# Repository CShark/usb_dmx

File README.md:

# USB ArtNET Interface

This project is a USB ArtNET interface with four ports, based on the STM32G484. It will register itself as an Ethernet Card using the CDC-NCM protocoll to be automatically recognized by most operating systems (except Windows 10, which needs some manual configuration). It will then bind the ArtNET-implementation to a configurable IP on that virtual ethernet card. The device can be configured either using ArtNET commands for software that supports this, using a web interface on the device and it can optionally be extended to include a display module for configuration directly at the device.

## Schematic
The project uses an STM32G484RE, but should work with any STM32G4xxRE variant. The ports are controlled by a MAX3440E each, which will provide some ESD protection in addition to the TVS-Diodes. The device will draw around ~150mA, which is easily delivered by USB2.0 ports. Galvanic isolation was omitted because it needs too much space and because it is not recommended for the transmitting ports of DMX-Devices anyway (although it is recommended for receiving ports, but not mandatory).

## PCB
The PCB is designed as a four layer board, as with this small size the price was acceptable. The pcb was designed with a `TEKAL 31.29`-case from TEKO in mind, but any case with at least 100x100mm will work.  placing three ports at the rear and one port beside the usb port at the front of the case. The display module is completely optional and is designed to slot into the mainboard and is secured with an additional screw from the front. It is then connected using a 10-pin ribbon cable.

### BOM
The total cost for this device is currently aproximately 90€. Assembly takes around 6 hours, including soldering the boards, CNC the covers and soldering / crimping the connectors. You can save money by printing your own case (25€), finding a cheaper STM32G4xxRE variant at your local dealer (11€), finding cheaper XLR connectors (5€) and skipping on the display module (5€). 

<details>
<summary>Mainboard (~40€)</summary>

| Amount | Type | Value | Footprint |
|-|-|-|-|
| 4 | Capacitor | 1μF | 0603 |
| 7 | Capacitor | 100nF | 0603 |
| 2 | Capacitor | 20pF | 0603 |
| 1 | Capacitor | 10nF | 0603 |
| 1 | Capacitor | 4.7μF | 0603 |
| 8 | TVS Diode | | SMA |
| 1 | USB-C Receptacle | | |
| 1 | FFC Connector | | 1x10, Pitch 1mm |
| 4 | Terminal Block | | 1x3, Pitch 2.54mm |
| 1 | Pin Header | | 1x3, Pitch 2.54mm |
| 1 | Jumper | | 1x2, Pitch 2.54mm |
| 2 | Resistor | 5K1 | 0603 |
| 1 | Resistor | 4K7 | 0603 |
| 4 | Resistor | 130 | 0603 |
| 8 | Resistor | 560 | 0603 |
| 1 | Switch | | Through Hole, Height 6mm |
| 1 | Switch | | Through Hole, Angled, Height 6mm |
| 1 | DIP-Switch | | Through Hole, 2x4, Pitch 2.54mm |
| 1 | ESD Protection | ESDALD05UD4 | SOT23-6 |
| 1 | Linear Regulator | AP2112K-3.3 | SOT23-5 |
| 4 | Transceiver | MAX3440E | SOIC-8 |
| 1 | Crystal | 25MHz | HC49 |
| 1 | μC | STM32G484RE | LQFP64 |
    
</details>

<details>
<summary>Display Board (~5€)</summary>

| Amount | Type | Footprint |
|-|-|-|
| 1 | OLED-Display | 0.96" with I²C and SSD1306 compatible driver |
| 1 | FFC Connector | 1x10, Pitch 1mm |
| 2 | Resistor | 4K7 | 0603 |
| 4 | Switch | Through Hole, Height 10mm |
| 1 | FFC Cable | 1x10, Pitch 1mm, Length ~100mm, Type B (opposing-side contacts) |

</details>

<details>
<summary>Mechanical parts (~40€)</summary>

| Amount | Type | Specs |
|-|-|-|
| 1 | Case | TEKO TEKAL 31.29, or any case that takes Eurocard-sized PCBs (100x100mm) |
| 4 | XLR Connector | An individual mix of Female and Male XLR 3- and 5-Pin connectors, depending on your needs |
| 9 | Screws | M2, Length 15mm, Countersink |
| 9 | Nuts | M2 |
| 1 | Acrylic Window | 15mm x 25mm |
| 1 | Spacer | M2, Length 6mm |
| 1 | Mainboard PCB | | 
| 1 | Display PCB | |

</details>

Here are two lists on digikey that include all necessary components, except for the mechanical parts and the oled-display. It does contain four XLR-Connectors though.
- [Parts for the Mainboard](https://www.digikey.com/en/mylists/list/8UBRGNUC4X)
- [Parts for the Display-Module](https://www.digikey.com/en/mylists/list/5N5ETFD0BY)

## Firmware
The firmware is completely custom, only based on CMSIS (no HAL) and supports the important parts of the ArtNET protocol. Which port is an input and which an output can be set using the dip switches, but later be overwritten using either ArtNET commands, the WebUI or the display menu. The device also has a reset button to reset the configuration for when things go completely wrong. If the device is completely bricked it can be put into bootloader mode using a jumper on the mainboard.

The device supports mDNS and is always reachable using `artnet.local` in addition to its ip-address. The WebUI allows configuring each individual port with all the settings that ArtNET-Commands also support. You can also change the ip-configuration of the device and its internal minimal DHCP-Server, as well as clearing all settings, rebooting the device and switching the device into DFU/Bootloader mode to flash a new firmware.

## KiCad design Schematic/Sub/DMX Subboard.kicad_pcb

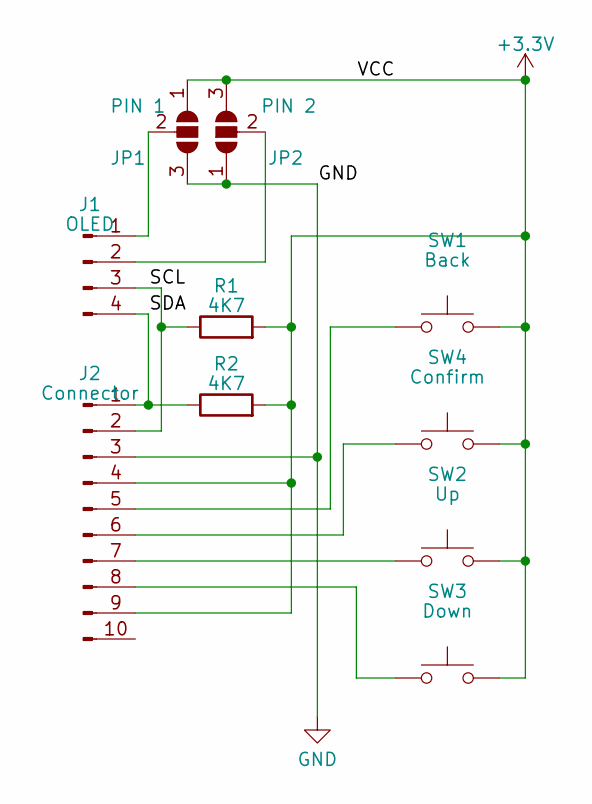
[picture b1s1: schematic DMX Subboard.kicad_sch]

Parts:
J1: OLED; PinHeader_1x04_P2.54mm_Vertical
J2: Connector; TE_1-84952-0_1x10-1MP_P1.0mm_Horizontal
JP1: PIN 1; SolderJumper-3_P2.0mm_Open_TrianglePad1.0x1.5mm
JP2: PIN 2; SolderJumper-3_P2.0mm_Open_TrianglePad1.0x1.5mm
R1, R2: 4K7; R_0603_1608Metric_Pad0.98x0.95mm_HandSolder
SW1: Back; SW_PUSH_6mm_H8.5mm
SW2: Up; SW_PUSH_6mm_H8.5mm
SW3: Down; SW_PUSH_6mm_H8.5mm
SW4: Confirm; SW_PUSH_6mm_H8.5mm

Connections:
+3.3V: J2.4, J2.9, JP1.1 (A), JP2.3 (B), R1.2, R2.2, SW1.2, SW2.2, SW3.2, SW4.2
/SCL: J1.3, J2.2, R1.1
/SDA: J1.4, J2.1, R2.1
GND: J2.3, JP1.3 (B), JP2.1 (A)
unnamed: J1.1, JP1.2 (C)
unnamed: J1.2, JP2.2 (C)
unnamed: J2.5, SW1.1
unnamed: J2.6, SW4.1
unnamed: J2.7, SW2.1
unnamed: J2.8, SW3.1

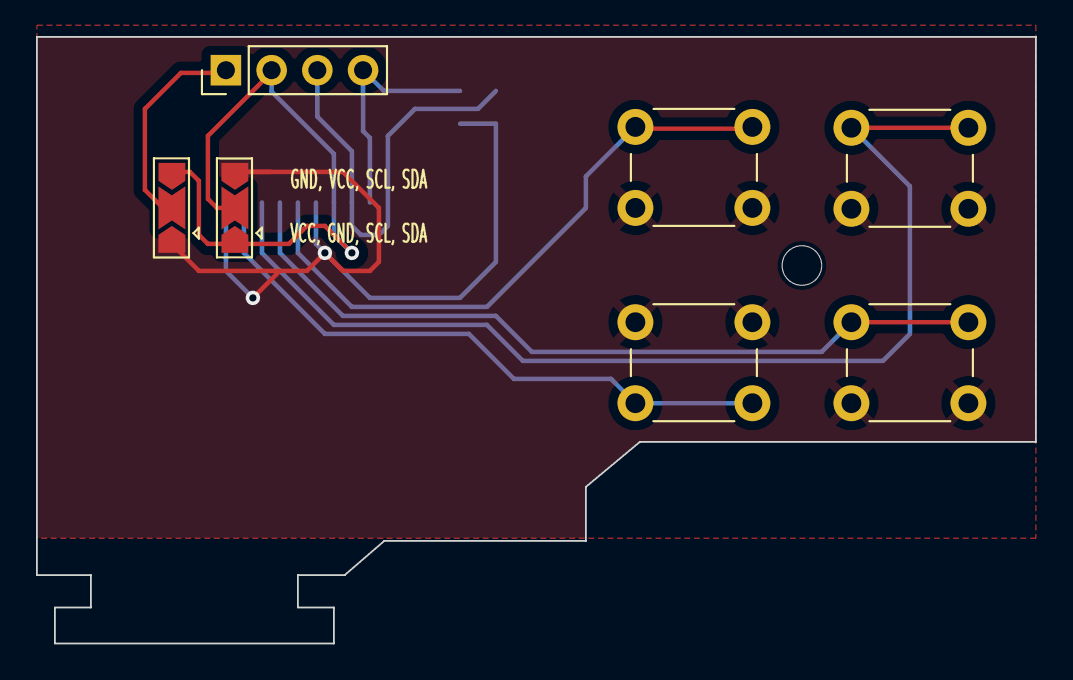
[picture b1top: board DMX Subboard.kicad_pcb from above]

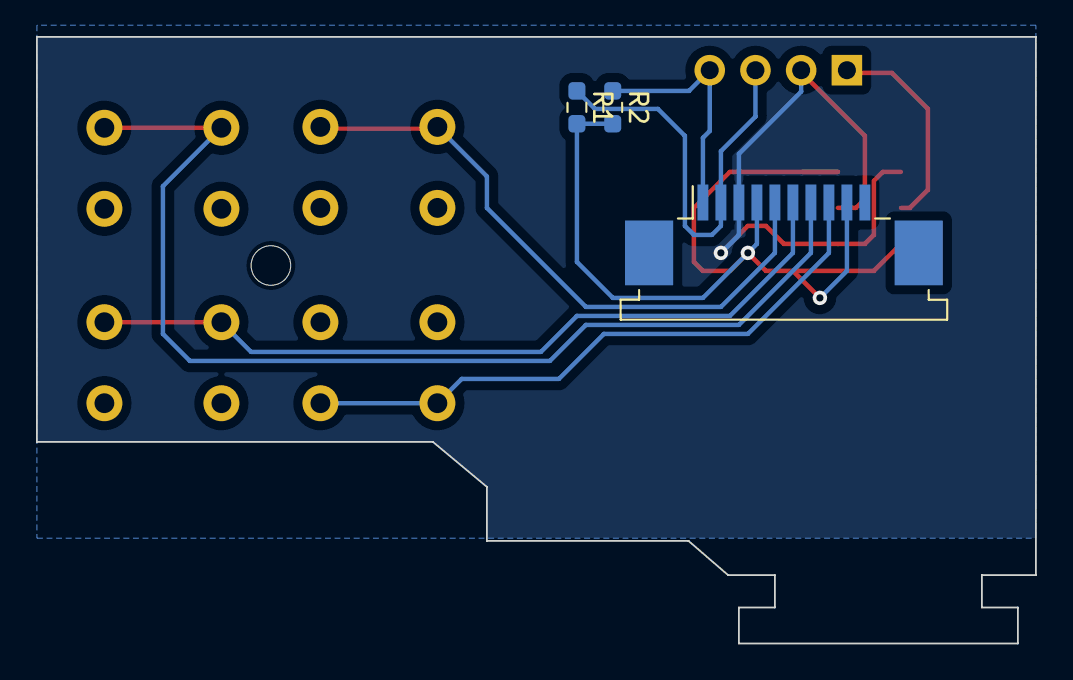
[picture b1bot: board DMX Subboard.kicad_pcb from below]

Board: 2 copper layers, 55.5 x 33.7 mm, 10 parts (3 on the bottom side), 10 nets.

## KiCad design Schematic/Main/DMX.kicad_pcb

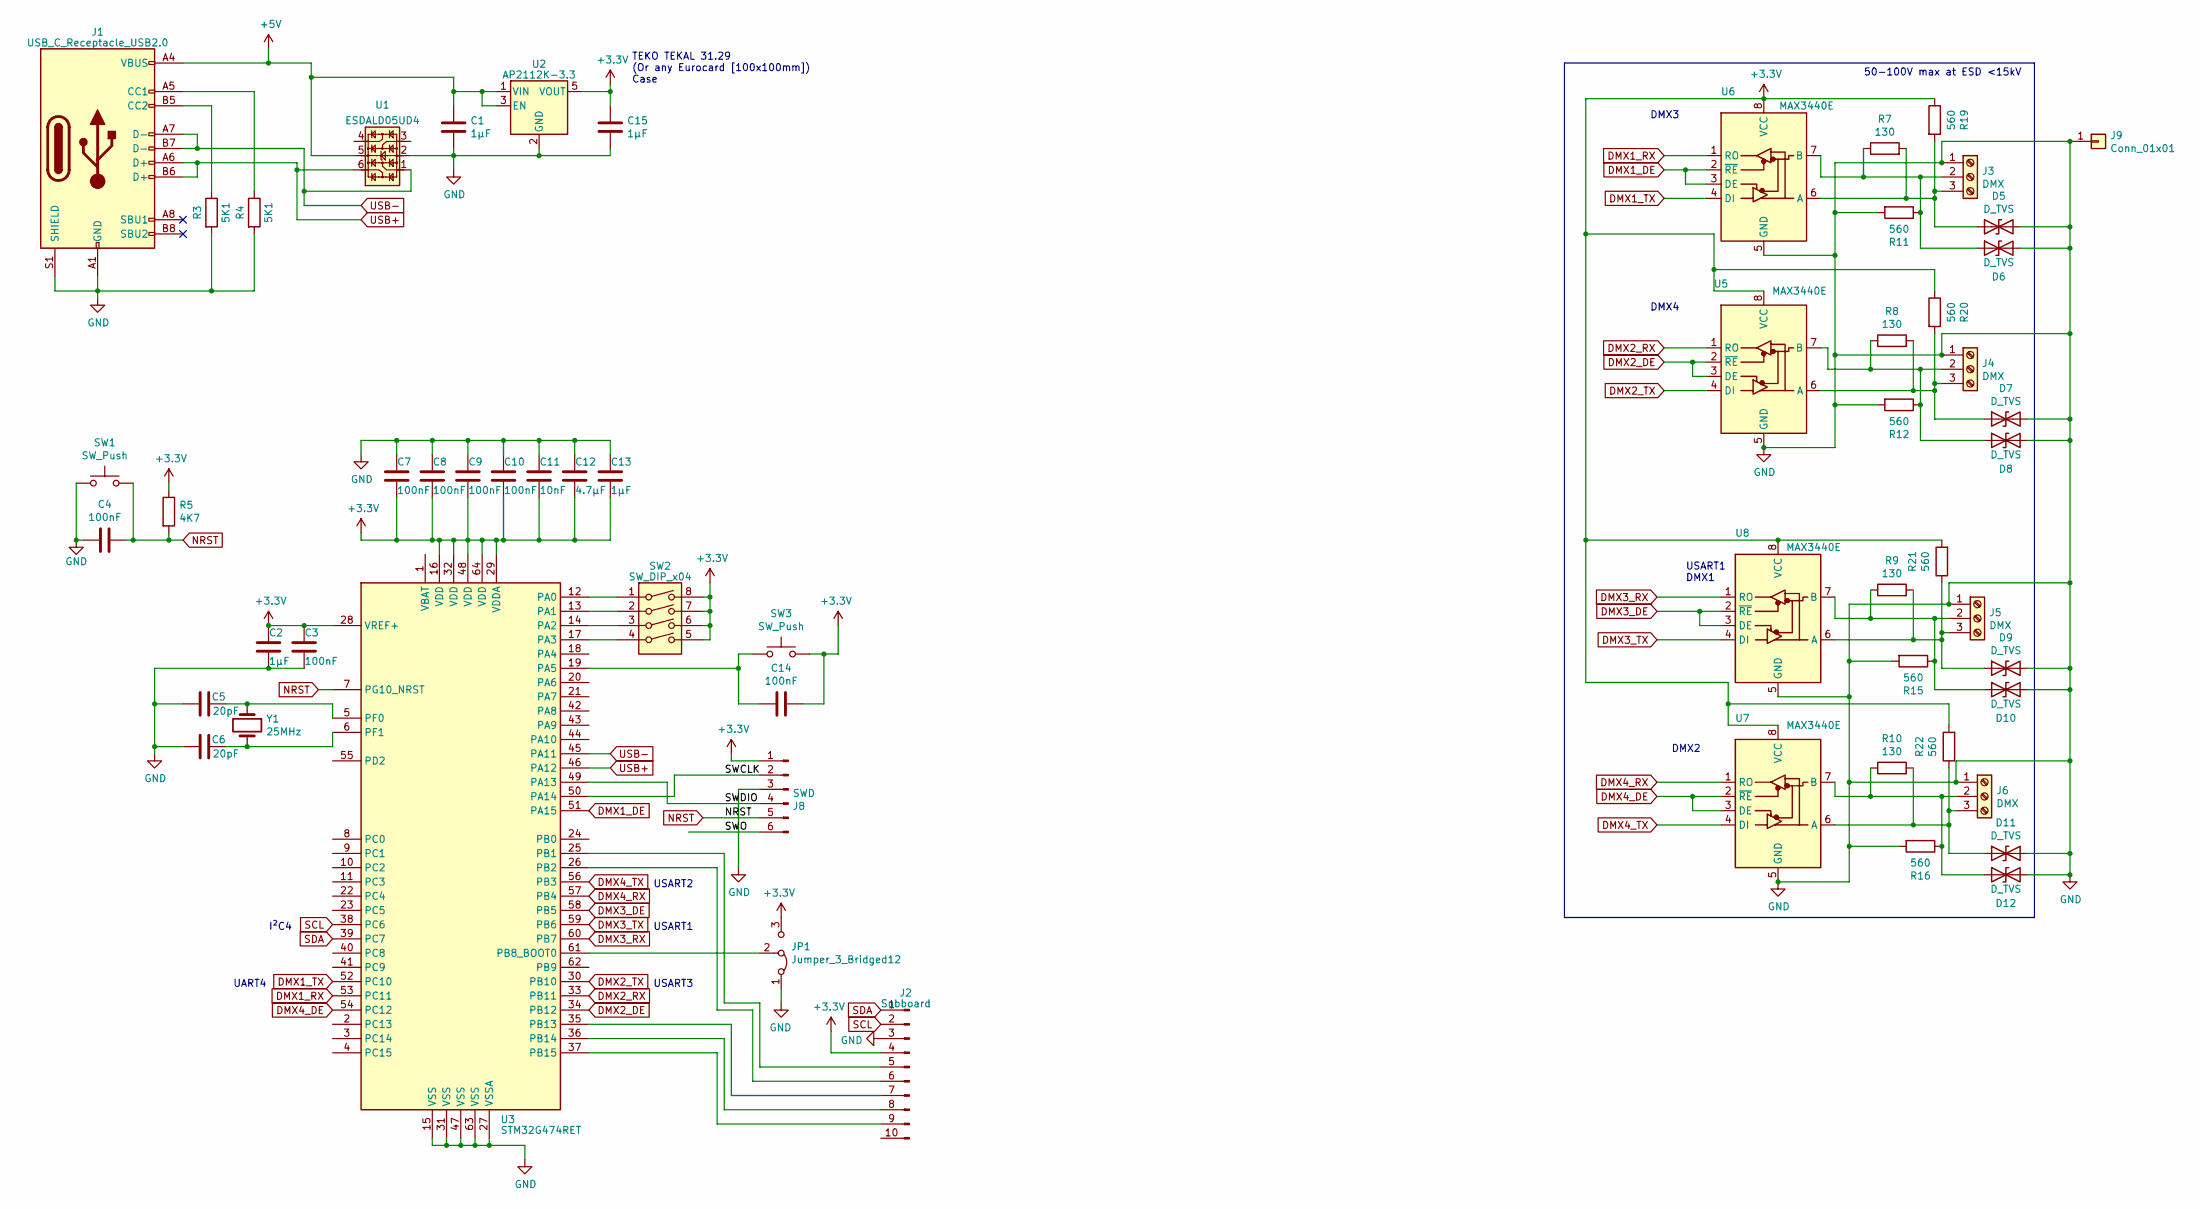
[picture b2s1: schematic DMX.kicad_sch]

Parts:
C1, C2, C13, C15: 1μF; C_0603_1608Metric_Pad1.08x0.95mm_HandSolder
C3, C4, C7, C8, C9, C10, C14: 100nF; C_0603_1608Metric_Pad1.08x0.95mm_HandSolder
C5, C6: 20pF; C_0603_1608Metric_Pad1.08x0.95mm_HandSolder
C11: 10nF; C_0603_1608Metric_Pad1.08x0.95mm_HandSolder
C12: 4.7μF; C_0603_1608Metric_Pad1.08x0.95mm_HandSolder
D5, D6, D7, D8, D9, D10, D11, D12: D_TVS; D_SMA_Handsoldering
J1: USB_C_Receptacle_USB2.0; USB_C_Receptacle_HRO_TYPE-C-31-M-12
J2: Subboard; TE_1-84953-0_1x10-1MP_P1.0mm_Horizontal
J3, J4, J5, J6: DMX; TerminalBlock_Altech_AK300-3_P5.00mm
J8: SWD; PinHeader_1x06_P2.54mm_Vertical
J9: Conn_01x01; MountingHole_4.3mm_M4_DIN965_Pad
JP1: Jumper_3_Bridged12; PinHeader_1x03_P2.54mm_Vertical
R3, R4: 5K1; R_0603_1608Metric_Pad0.98x0.95mm_HandSolder
R5: 4K7; R_0603_1608Metric_Pad0.98x0.95mm_HandSolder
R7, R8, R9, R10: 130; R_0603_1608Metric_Pad0.98x0.95mm_HandSolder
R11, R12, R15, R16, R19, R20, R21, R22: 560; R_0603_1608Metric_Pad0.98x0.95mm_HandSolder
SW1: SW_Push; SW_PUSH_6mm
SW2: SW_DIP_x04; DIP-8_W7.62mm
SW3: SW_Push; SW_Tactile_SPST_Angled_PTS645Vx39-2LFS
U1: ESDALD05UD4; SOT-23-6_Handsoldering
U2: AP2112K-3.3; SOT-23-5_HandSoldering
U3: STM32G474RET; LQFP-64_10x10mm_P0.5mm
U5, U6, U7, U8: MAX3440E; SOIC-8_3.9x4.9mm_P1.27mm
Y1: 25MHz; Crystal_HC18-U_Vertical

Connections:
+3V3: C2.1, C3.1, C7.2, C8.2, C9.2, C10.2, C11.2, C12.2, C13.2, C14.2, C15.1, J2.4, J8.1, JP1.3 (B), R5.1, R19.1, R20.1, R21.2, R22.2, SW2.5, SW2.6, SW2.7, SW2.8, SW3.1, U2.5 (VOUT), U3.16 (VDD), U3.28 (VREF+), U3.29 (VDDA), U3.32 (VDD), U3.48 (VDD), U3.64 (VDD), U5.8 (VCC), U6.8 (VCC), U7.8 (VCC), U8.8 (VCC)
+5V: C1.1, J1.A4 (VBUS), J1.A9 (VBUS), J1.B4 (VBUS), J1.B9 (VBUS), U1.5, U2.1 (VIN), U2.3 (EN)
/SWCLK: J8.2, U3.50 (PA14)
/SWDIO: J8.4, U3.49 (PA13)
/SWO: J8.6
DMX1_DE: U3.51 (PA15), U6.2 (~RE), U6.3 (DE)
DMX1_RX: U3.53 (PC11), U6.1 (RO)
DMX1_TX: U3.52 (PC10), U6.4 (DI)
DMX2_DE: U3.34 (PB12), U5.2 (~RE), U5.3 (DE)
DMX2_RX: U3.33 (PB11), U5.1 (RO)
DMX2_TX: U3.30 (PB10), U5.4 (DI)
DMX3_DE: U3.58 (PB5), U8.2 (~RE), U8.3 (DE)
DMX3_RX: U3.60 (PB7), U8.1 (RO)
DMX3_TX: U3.59 (PB6), U8.4 (DI)
DMX4_DE: U3.54 (PC12), U7.2 (~RE), U7.3 (DE)
DMX4_RX: U3.57 (PB4), U7.1 (RO)
DMX4_TX: U3.56 (PB3), U7.4 (DI)
GND: C1.2, C2.2, C3.2, C4.2, C5.2, C6.2, C7.1, C8.1, C9.1, C10.1, C11.1, C12.1, C13.1, C15.2, D5.2 (A2), D6.2 (A2), D7.2 (A2), D8.2 (A2), D9.2 (A2), D10.2 (A2), D11.2 (A2), D12.2 (A2), J1.A1 (GND), J1.A12 (GND), J1.B1 (GND), J1.B12 (GND), J1.S1 (SHIELD), J2.3, J3.1, J4.1, J5.1, J6.1, J8.3, J9.1, JP1.1 (A), R3.2, R4.2, R11.2, R12.2, R15.2, R16.2, SW1.1, U1.2, U2.2 (GND), U3.15 (VSS), U3.27 (VSSA), U3.31 (VSS), U3.47 (VSS), U3.63 (VSS), U5.5 (GND), U6.5 (GND), U7.5 (GND), U8.5 (GND)
NRST: C4.1, J8.5, R5.2, SW1.2, U3.7 (PG10_NRST)
unnamed: D5.1 (A1), J3.3, R7.2, R19.2, U6.6 (A)
unnamed: D6.1 (A1), J3.2, R7.1, R11.1, U6.7 (B)
unnamed: D7.1 (A1), J4.3, R8.2, R20.2, U5.6 (A)
unnamed: D8.1 (A1), J4.2, R8.1, R12.1, U5.7 (B)
unnamed: D9.1 (A1), J5.3, R9.2, R21.1, U8.6 (A)
unnamed: D10.1 (A1), J5.2, R9.1, R15.1, U8.7 (B)
unnamed: D11.1 (A1), J6.3, R10.2, R22.1, U7.6 (A)
unnamed: D12.1 (A1), J6.2, R10.1, R16.1, U7.7 (B)
unnamed: J1.A5 (CC1), R4.1
unnamed: J1.B5 (CC2), R3.1
unnamed: J2.5, U3.25 (PB1)
unnamed: J2.6, U3.26 (PB2)
unnamed: J2.7, U3.35 (PB13)
unnamed: J2.8, U3.36 (PB14)
unnamed: J2.9, U3.37 (PB15)
unnamed: JP1.2 (C), U3.61 (PB8_BOOT0)
unnamed: SW2.1, U3.12 (PA0)
unnamed: SW2.2, U3.13 (PA1)
unnamed: SW2.3, U3.14 (PA2)
unnamed: SW2.4, U3.17 (PA3)
unnamed: C14.1, SW3.2, U3.19 (PA5)
unnamed: C5.1, U3.5 (PF0), Y1.1
unnamed: C6.1, U3.6 (PF1), Y1.2
SCL: J2.2, U3.38 (PC6)
SDA: J2.1, U3.39 (PC7)
USB+: J1.A6 (D+), J1.B6 (D+), U1.6, U3.46 (PA12)
USB-: J1.A7 (D-), J1.B7 (D-), U1.1, U3.45 (PA11)

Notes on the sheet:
I²C4
USART1 DMX1
50-100V max at ESD <15kV
TEKO TEKAL 31.29 (Or any Eurocard [100x100mm]) Case
USART3
UART4
DMX4
USART2
DMX2
DMX3
USART1

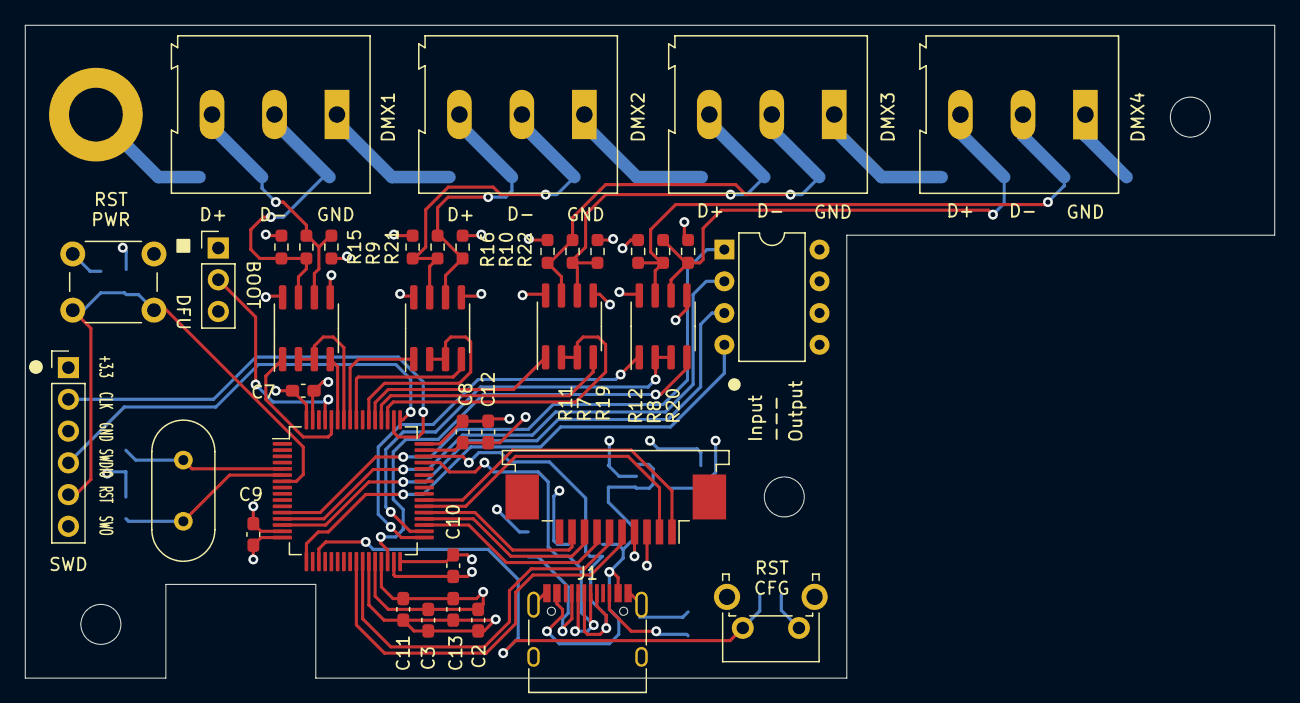
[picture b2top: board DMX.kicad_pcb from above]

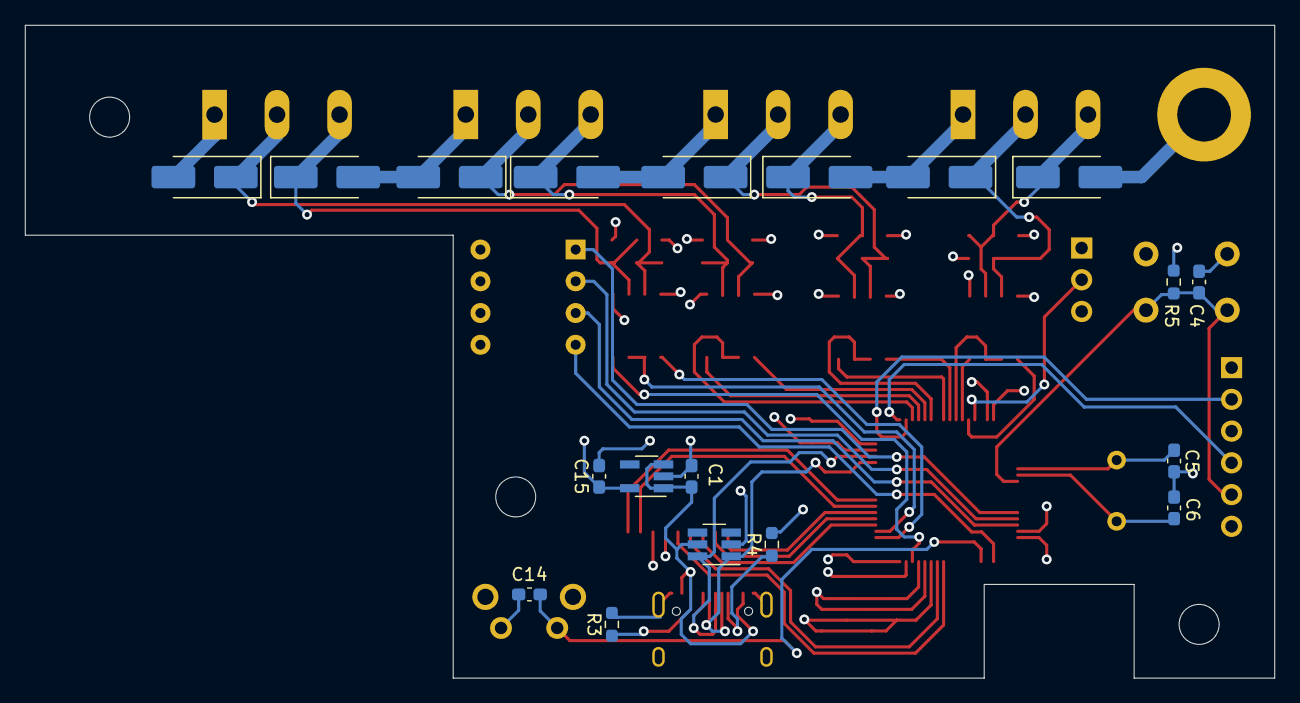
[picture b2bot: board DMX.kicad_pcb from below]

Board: 4 copper layers, 100.0 x 52.2 mm, 58 parts (20 on the bottom side), 45 nets.

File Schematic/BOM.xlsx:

# | Reference | Qty | Value | Footprint | DNP
1 | C1, C2, C13, C15 | 4 | 1μF | Capacitor_SMD:C_0603_1608Metric_Pad1.08x0.95mm_HandSolder
2 | C3, C4, C7, C8, C9, C10, C14 | 7 | 100nF | Capacitor_SMD:C_0603_1608Metric_Pad1.08x0.95mm_HandSolder
3 | C5, C6 | 2 | 20pF | Capacitor_SMD:C_0603_1608Metric_Pad1.08x0.95mm_HandSolder
4 | C11 | 1 | 10nF | Capacitor_SMD:C_0603_1608Metric_Pad1.08x0.95mm_HandSolder
5 | C12 | 1 | 4.7μF | Capacitor_SMD:C_0603_1608Metric_Pad1.08x0.95mm_HandSolder
6 | D5, D6, D7, D8, D9, D10, D11, D12 | 8 | D_TVS | Diode_SMD:D_SMA_Handsoldering
7 | J1 | 1 | USB_C_Receptacle_USB2.0 | Connector_USB:USB_C_Receptacle_HRO_TYPE-C-31-M-12
8 | J2 | 1 | Subboard | Connector_FFC-FPC:TE_1-84953-0_1x10-1MP_P1.0mm_Horizontal
9 | J3, J4, J5, J6 | 4 | DMX | TerminalBlock:TerminalBlock_Altech_AK300-3_P5.00mm
10 | J9 | 1 | Conn_01x01 | MountingHole:MountingHole_4.3mm_M4_DIN965_Pad
11 | JP1 | 1 | Jumper_3_Bridged12 | Connector_PinHeader_2.54mm:PinHeader_1x03_P2.54mm_Vertical
12 | R3, R4 | 2 | 5K1 | Resistor_SMD:R_0603_1608Metric_Pad0.98x0.95mm_HandSolder
13 | R5 | 1 | 4K7 | Resistor_SMD:R_0603_1608Metric_Pad0.98x0.95mm_HandSolder
14 | R7, R8, R9, R10 | 4 | 130 | Resistor_SMD:R_0603_1608Metric_Pad0.98x0.95mm_HandSolder
15 | R11, R12, R15, R16, R19, R20, R21, R22 | 8 | 560 | Resistor_SMD:R_0603_1608Metric_Pad0.98x0.95mm_HandSolder
16 | SW1 | 1 | SW_Push | Button_Switch_THT:SW_PUSH_6mm
17 | SW2 | 1 | SW_DIP_x04 | Package_DIP:DIP-8_W7.62mm
18 | SW3 | 1 | SW_Push | Button_Switch_THT:SW_Tactile_SPST_Angled_PTS645Vx39-2LFS
19 | U1 | 1 | ESDALD05UD4 | Package_TO_SOT_SMD:SOT-23-6_Handsoldering
20 | U2 | 1 | AP2112K-3.3 | Package_TO_SOT_SMD:SOT-23-5_HandSoldering
21 | U3 | 1 | STM32G474RET | Package_QFP:LQFP-64_10x10mm_P0.5mm
22 | U5, U6, U7, U8 | 4 | MAX3440E | Package_SO:SOIC-8_3.9x4.9mm_P1.27mm
23 | Y1 | 1 | 25MHz | Crystal:Crystal_HC18-U_Vertical

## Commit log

2022-09-03 Send DMX works
    First USB steps
2022-09-18 Working DMX-USB HID Interface & DMX-Out
2022-09-20 DMX RX works now
2022-11-06 Bugfix for DMX Transmit
    USART-Clock now uses HSE
2022-11-06 Moved Datasheets
2022-11-06 Added schematic and pcb layout
2022-11-06 Added QLC+ changes for ease of use
2022-11-06 Added some images for readme
2022-11-06 Added license
2022-11-06 Added README
    Made reported USB configuration follow the USART configuration
2022-12-01 Outputs/Inputs can now be configured using the resistors
    Fixes #1
2022-12-01 HID-Version complete
2022-12-30 Partial bugfix for windows update
2022-12-31 Added perliminary ArtNet-Support using NCM and lwip
2023-01-10 DMX Output via ArtNet works now
    Emergency COM-Port if device is broken
    Switch to bootloader possible
    Doubled the core clock speed
2023-01-30 Some memory savings
    Some terminal commands for emergency management
    Persistent settings using a single flash page and Virtual Addressing
2023-02-05 Working Flash-EEPROM implementation
    Moving some of the settings to the config module for permanent storage
2023-02-08 Add the ArtNet.Config tool & Update readme
2023-02-08 Some Bugfixes & ArtNet features
    - Store ACN Priority in config
    - Support for Failover modes
    - Fix Bug when changing port mode to delta
    - Support to override port direction with ArtNET
    - Store Port Flags (Delta-Mode & RDM) in config
    - ArtNET Timeout to detect inactive ports for failover
2023-02-09 Adding profiler
    Reordering some initialization to speed up the boot sequence
2023-02-09 Faster USB-Enumeration
    Forgot to reject the Request for a qualifier descriptor used for High Speed devices
2023-02-09 Fix bugs in ArtNET Input ports
2023-02-10 First completely working ArtNET version
    Added profiling feature to ignore sessions after they started
    Doubled the AHB clock, now it works stable somehow?
    Better Input handling without dropping packets
    Missing: Still some serial commands
2023-02-18 Finished first version of ArtNET
    Limit DMX from Input to once per second if no changes happen
    Disable inputs moved to config
2023-02-20 Minor bugfixes
    Input Channel count was encoded in wrong endian
    Marked USB-SRAM as noload, otherwise DFU will throw errors
2023-02-20 Set Firmware version for first Release
2023-02-27 Bugfix for DMX Input
    Fixed off-by-1 bug in the compiler optimized firmware
    Added D0 command to dump dmx buffers for Debug purposes via serial
2023-02-28 Bugfix for serial device detection
2023-03-06 Bugfix for receiving non-DMX packets and flickering
2023-05-29 Started new Hardware Revision
    Fixes #6
2023-06-08 Update README.md
    Some price adjustments
2023-06-12 Porting Code to new MCU
    - Add BOM at digikey
    - Adjusting port config to dip switches
    - More resources to lwip stack
2023-06-13 ArtNET poll reply is now per port for more configuration flexibility
2023-06-13 Renaming project to avoid spaces
2023-06-13 Removed all warnings in the project
2023-06-16 Adding initial WebUI support
    - Removing serial interface completely
2023-07-07 First OLED support
    - SSD1306 support added
    - OLED menu added (wip)
2023-07-11 OLED support
    - can now apply settings through the OLED module
2023-07-12 Some minor bugfixes
    - Implemented reset button
    - "Fixed" timing bug with OLED initialization
    - Fixed Release Build
    - Fixed Flash settings
2023-07-14 Added Cutout specifications
2023-07-24 Added support for different OLED-pinning
2023-07-29 CAD adjustments
    - Adjusted Distance of front XLR, was too close to cover border
    - Adjusted Milling parameters for my CNC: The plastic melts really fast. 100mm/m | 0.5mm @ 10.000RPM worked for me with acceptable burring. Cleaning up with a knife was necessary afterwards though
2023-08-08 Fixing all the configuration issues
    OLED:
    - Hardfault when up/down button was pressed in IP overview
    - ArtNET-Universe was not set correctly
    - Description text did not scroll correctly
    Flash:
    - Reset status correctly when clearing config page
2023-08-08 Fixed bug in initialization of first port
    - All tests completed
2023-08-08 Fixing most of the Warnings
2023-08-08 Update README.md
    Fixed filename typo
2023-08-11 Removed deprecated ArtNET cli
2023-11-06 - Fixed bug with renewing DHCP address
2024-02-21 Some refactoring
    - Better USB Config descriptor representation now without copying
    - Proper handling of unsupported USB commands
    - Refactoring of USART routines to support RDM later
2024-03-26 Decoupling USART and DMX for easier RDM implementation
2024-03-26 First changes for RDM
2024-03-28 Fix submodule
    Update Version number
2024-04-07 Some bugfixes for input ports
    - New Input is now triggered correctly
2024-12-16 Fixed bug in USB handler that prevented iPads from using this device
    Fixes #13
